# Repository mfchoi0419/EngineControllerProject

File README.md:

# Engine Controller Project

Remote engine control and monitoring system for a small internal combustion engine used in a combined heat and power (CHP) biodigester application.

## Overview

This project uses a Raspberry Pi/BeagleBone-hosted web interface to communicate with an Arduino Uno over serial USB in order to remotely control and monitor a Honda GX35 engine.

The system was developed for a senior design project focused on biodigester thermal management and electrical generation using biogas fuel.

Features:
- Remote electric start/top
- Choke servo control
- Gas solenoid control
- Oil pump control
- Magneto kill control
- Temperature monitoring
- O2 sensor integration
- Real-time web dashboard
- Local WiFi hotspot operation without internet

## System Architecture

Frontend:
- HTML
- CSS
- JavaScript

Backend:
- Python Flask Server
- Serial Communication over USB

Host Devices:
- Raspberry Pi Model 3 b
- BeagleBone Black

## Hardware Components
- Honda GX35 engine
- Arduino Uno
- Raspberry Pi / BeagleBone Black
- MOSFET switching circuits
- Relay-controlled starter system
- Thermistor temperature sensors
- O2 sensor system
- Oil cooling pump
- Fuel shutoff solenoid

## Features

### Remote Engine Start
The web interface sends commands to the backend Flask server, which transmits serial commands to the Arduino for starter actuation.

### Sensor Monitoring
The systemm readss:
- Engine temperature
- Oil temperature
- O2 sensor voltage

Data is displayed live through the browser interface.

### Offline Operation
The Raspberry Pi can host its own WiFi hotspot, allowing local engine control without internet access.

## Repository Structure
```text
Engine_Controller/            -> Arduino firmware
Engine_Controller_Backend/    -> Flask backend + web server
PCB_Design/                   -> PCB and hardware design files

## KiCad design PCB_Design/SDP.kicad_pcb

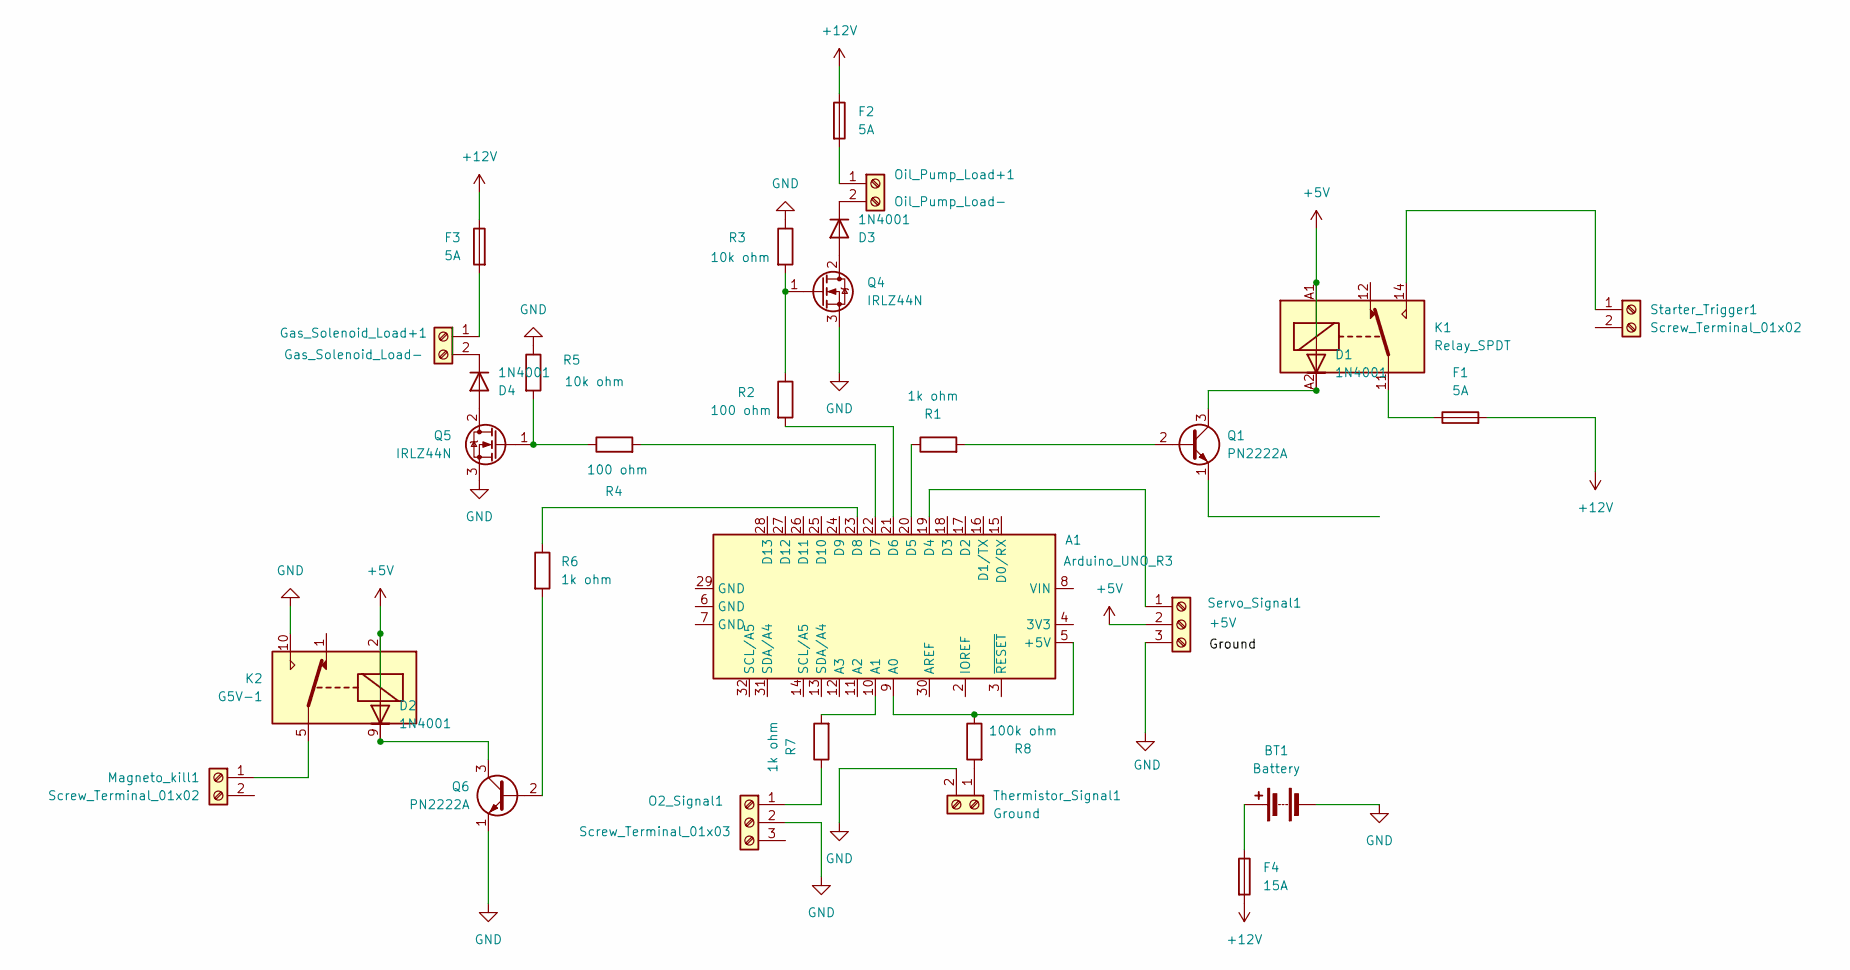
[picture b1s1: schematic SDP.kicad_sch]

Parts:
A1: Arduino_UNO_R3
BT1: Battery; PinHeader_1x02_P2.54mm_Vertical
D1, D2, D3, D4: 1N4001; D_DO-41_SOD81_P10.16mm_Horizontal
F1, F2, F3: 5A; Fuseholder_Blade_ATO_Littelfuse_Pudenz_2_Pin
F4: 15A; Fuseholder_Blade_Mini_Keystone_3568
Gas_Solenoid_Load+1: Gas_Solenoid_Load-; PinHeader_1x02_P2.54mm_Vertical
K1: Relay_SPDT; Relay_SPDT_Finder_34.51_Horizontal
K2: G5V-1; Relay_SPDT_Omron_G5V-1
Magneto_kill1: Screw_Terminal_01x02; PinHeader_1x02_P2.54mm_Vertical
O2_Signal1: Screw_Terminal_01x03; PinHeader_1x02_P2.54mm_Vertical
Oil_Pump_Load+1: Oil_Pump_Load-; PinHeader_1x02_P2.54mm_Vertical
Q1, Q6: PN2222A; TO-92_Inline
Q4, Q5: IRLZ44N; TO-220-3_Vertical
R1, R6, R7: 1k ohm; R_Axial_DIN0207_L6.3mm_D2.5mm_P10.16mm_Horizontal
R2, R4: 100 ohm; R_Axial_DIN0207_L6.3mm_D2.5mm_P10.16mm_Horizontal
R3, R5: 10k ohm; R_Axial_DIN0207_L6.3mm_D2.5mm_P10.16mm_Horizontal
R8: 100k ohm; R_Axial_DIN0207_L6.3mm_D2.5mm_P10.16mm_Horizontal
Servo_Signal1: +5V; PinHeader_1x03_P2.54mm_Vertical
Starter_Trigger1: Screw_Terminal_01x02; PinHeader_1x02_P2.54mm_Vertical
Thermistor_Signal1: Ground; PinHeader_1x02_P2.54mm_Vertical

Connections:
+5V: D1.2 (A), D2.2 (A), K1.A1, K2.2, Servo_Signal1.2
+12V: F1.2, F2.1, F3.1, F4.2
GND: BT1.2 (-), K2.10, O2_Signal1.2, Q4.3 (S), Q5.3 (S), Q6.1 (E), R3.1, R5.1, Servo_Signal1.3, Thermistor_Signal1.2
unnamed: A1.5 (+5V), A1.9 (A0), R8.1
unnamed: A1.10 (A1), R7.2
unnamed: A1.19 (D4), Servo_Signal1.1
unnamed: A1.20 (D5), R1.1
unnamed: A1.21 (D6), R2.2
unnamed: A1.22 (D7), R4.2
unnamed: A1.23 (D8), R6.1
unnamed: BT1.1 (+), F4.1
unnamed: D1.1 (K), K1.A2, Q1.3 (C)
unnamed: D2.1 (K), K2.9, Q6.3 (C)
unnamed: D3.2 (A), Q4.2 (D)
unnamed: D3.1 (K), Oil_Pump_Load+1.2
unnamed: D4.2 (A), Q5.2 (D)
unnamed: D4.1 (K), Gas_Solenoid_Load+1.2
unnamed: F1.1, K1.11
unnamed: F3.2, Gas_Solenoid_Load+1.1
unnamed: K2.5, K2.6, Magneto_kill1.1 (Pin_1_1)
unnamed: O2_Signal1.1, R7.1
unnamed: F2.2, Oil_Pump_Load+1.1
unnamed: Q1.2 (B), R1.2
unnamed: Q4.1 (G), R2.1, R3.2
unnamed: Q5.1 (G), R4.1, R5.2
unnamed: Q6.2 (B), R6.2
unnamed: K1.14, Starter_Trigger1.1 (Pin_1_1)
unnamed: R8.2, Thermistor_Signal1.1

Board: 2 copper layers, 31 parts (0 on the bottom side), 28 nets, no tracks yet.

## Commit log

2026-05-08 Add project details to README.md
2026-05-08 Initial engine controller upload
2026-05-08 Revise README with project overview and features
    Expanded project details and features for clarity.
